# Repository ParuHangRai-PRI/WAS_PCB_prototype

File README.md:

# PCB projects related to WAS
Created March 19 2026.
Paru Hang Rai

## Handheld WAS
Schematics of the Handheld version of WAS.

## USB PD
Schematics of the Type-C integration with USB-PD using CYPD-3177. Intended as a barrel jack connector replacement.

**Always maintain appropriate gitignore before pushing**

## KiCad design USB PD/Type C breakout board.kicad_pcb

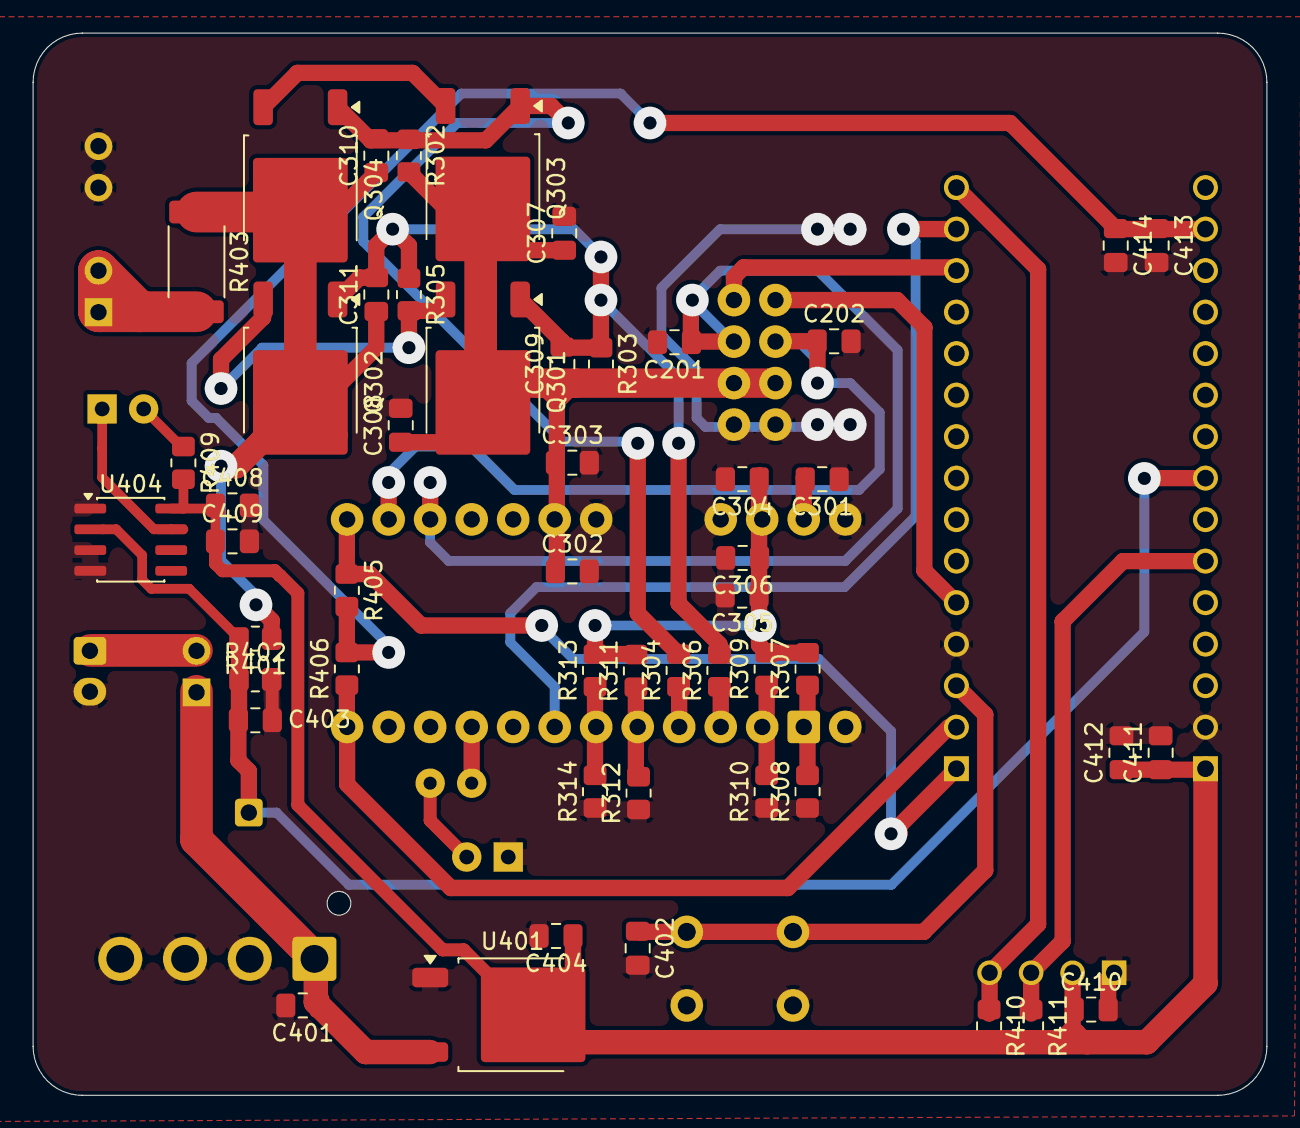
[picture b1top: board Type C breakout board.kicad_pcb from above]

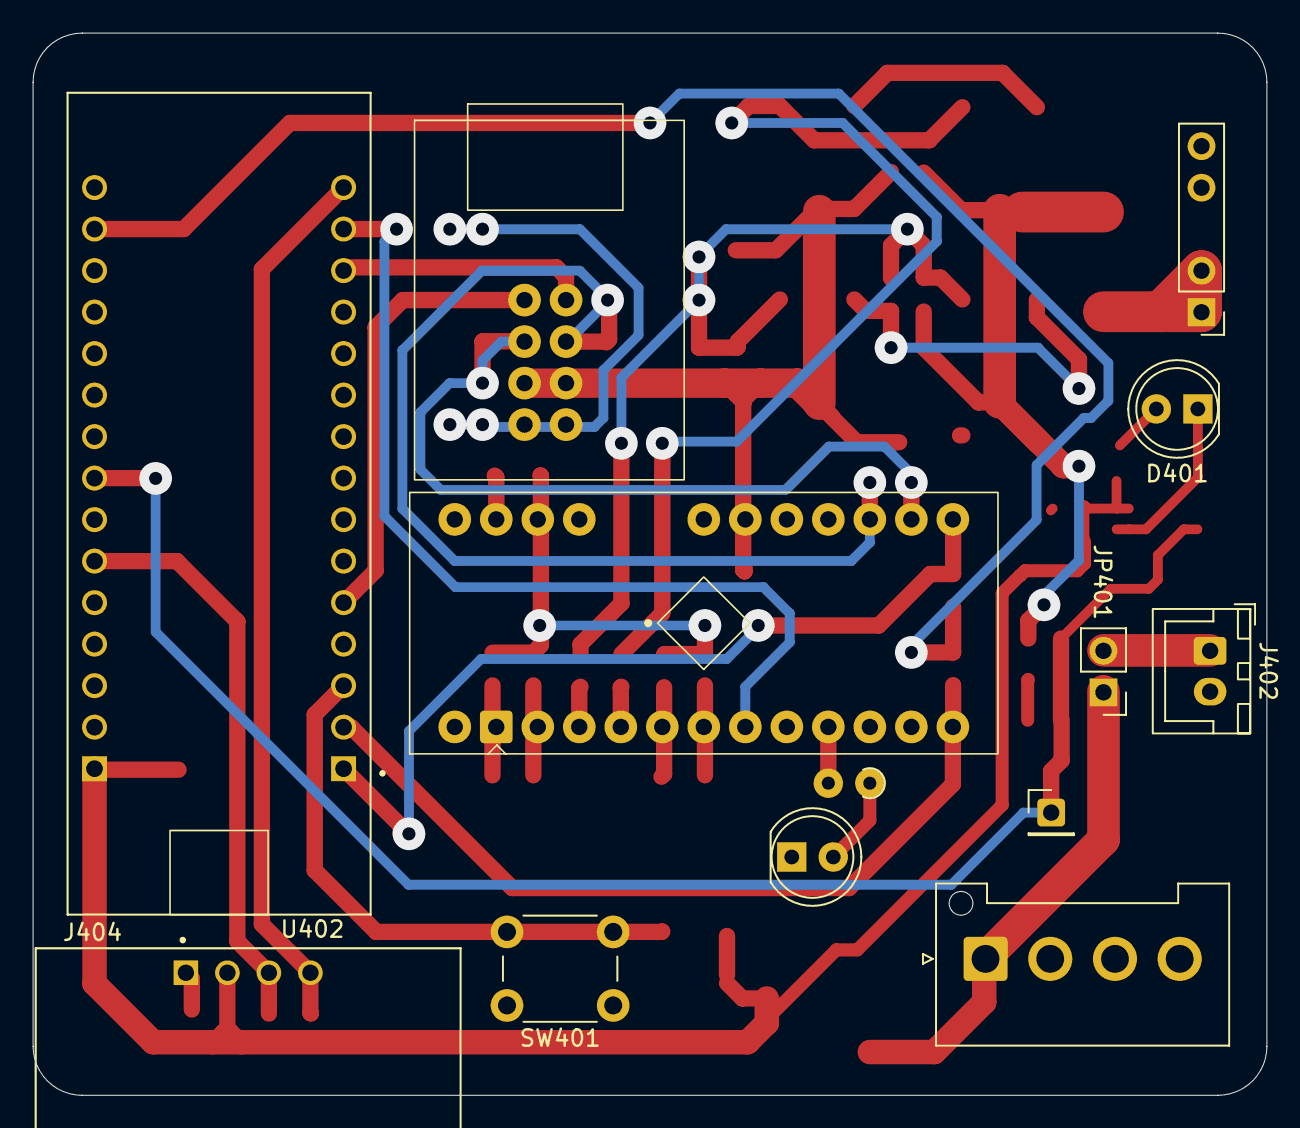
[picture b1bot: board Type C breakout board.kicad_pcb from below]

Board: 2 copper layers, 75.5 x 65.0 mm, 64 parts (13 on the bottom side), 35 nets.

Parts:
C201, C202: 330P; C_0805_2012Metric_Pad1.18x1.45mm_HandSolder
C301, C304, C307, C308, C309, C310, C311, C402, C403, C412, C413: 1u; C_0805_2012Metric_Pad1.18x1.45mm_HandSolder
C302, C401, C408: 10u; C_0805_2012Metric_Pad1.18x1.45mm_HandSolder
C303, C305, C306, C409, C410, C411, C414: 0.1u; C_0805_2012Metric_Pad1.18x1.45mm_HandSolder
C404: 22u; C_0805_2012Metric_Pad1.18x1.45mm_HandSolder
D301: LED; LED_D5.0mm
D401: LED-RED; LED_D5.0mm
J201: USB_C; Custom_USB_C
J401: Conn_01x04; JST_VH_B4P-VH-FB-B_1x04_P3.96mm_Vertical
J402: Conn_01x02; JST_XH_B2B-XH-A_1x02_P2.50mm_Vertical
J403: Conn_01x04; PinHeader_1x05_P2.54mm_Vertical
J404: OLED-Mount; OLED_0.96
JP401: Jumper_2_Open; PinHeader_1x02_P2.54mm_Vertical
Q301, Q302, Q303, Q304: PJD35P03; TO-252-2
R301: 220; R_Axial_DIN0204_L3.6mm_D1.6mm_P1.90mm_Vertical
R302, R305: 47k; R_0805_2012Metric_Pad1.20x1.40mm_HandSolder
R303: 10k; R_0805_2012Metric_Pad1.20x1.40mm_HandSolder
R304, R306: 1k; R_0805_2012Metric_Pad1.20x1.40mm_HandSolder
R307, R308, R309, R310, R311, R312, R313, R314: 5.1k; R_0805_2012Metric_Pad1.20x1.40mm_HandSolder
R401: 42k; R_0805_2012Metric_Pad1.20x1.40mm_HandSolder
R402: 8k; R_0805_2012Metric_Pad1.20x1.40mm_HandSolder
R403: 0.022R; R_2512_6332Metric_Pad1.40x3.35mm_HandSolder
R405, R406: 2.2k; R_0805_2012Metric_Pad1.20x1.40mm_HandSolder
R409: 150; R_0805_2012Metric_Pad1.20x1.40mm_HandSolder
R410, R411: 5k1; R_0805_2012Metric_Pad1.20x1.40mm_HandSolder
SW401: SW_Push; SW_PUSH_6mm_H4.3mm
TP401: TestPoint; PinHeader_1x01_P2.54mm_Vertical
U301: CYPD3177-24LQ; QFN_24-DIP
U401: AZ1117-5.0; TO-252-2
U402: NUCLEO-L432KC; MODULE_NUCLEO-L432KC
U404: LM311; SOIC-8_3.9x4.9mm_P1.27mm

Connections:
+3.3V: C304.1, C305.1, C306.1, R307.2, R309.2, R311.2, R313.2, U301.23 (VDDD)
+3V3_stm: C413.1, C414.1, R405.2, R406.2, U402.CN4_14 (+3V3)
+5V: C404.1, C408.1, C409.1, C410.1, C411.1, C412.1, J404.2, R409.2, R410.2, R411.2, U401.2 (VO), U402.CN4_1 (VIN), U404.8 (V+)
/CYPDD3177/+1.8V: C301.2, U301.24 (VCCD)
/CYPDD3177/FET_EN: R306.1, U301.3 (VBUS_FET_EN)
/CYPDD3177/FLT: R301.2, U301.9 (FAULT)
/CYPDD3177/IADJ_MAX: R311.1, R312.2, U301.5 (ISNK_COARSE)
/CYPDD3177/IADJ_MIN: R313.1, R314.2, U301.6 (ISNK_FINE)
/CYPDD3177/SAFE_EN: R304.1, U301.4 (SAFE_PWR_EN)
/CYPDD3177/VADJ_MAX: R309.1, R310.2, U301.2 (VBUS_MAX)
/CYPDD3177/VADJ_MIN: R307.1, R308.2, U301.1 (VBUS_MIN)
/test_ckt/NRST: C402.1, SW401.2, U402.CN3_3 (NRST_CN3)
/test_ckt/Vusb: C403.1, R401.2, R402.1, TP401.1 (1_1), U402.CN4_8 (PA5), U404.2 (+)
CC1: C201.1, J201.A5 (CC1), U301.15 (CC1)
CC2: C202.1, J201.B5 (CC2), U301.14 (CC2)
D+: J201.A6 (D+), J201.B6 (D+), U402.CN3_5 (PA12)
D-: J201.A7 (D-), J201.B7 (D-), U402.CN3_13 (PA11)
GND: C201.2, C202.2, C301.1, C302.2, C303.2, C304.2, C305.2, C306.2, C307.2, C308.2, C401.2, C402.2, C403.2, C404.2, C408.2, C409.2, C410.2, C411.2, C412.2, C413.2, C414.2, D301.1 (K), J201.A1 (GND), J201.A12 (GND), J201.B1 (GND), J201.B12 (GND), J401.2, J401.3, J401.4, J402.2, J403.3, J403.4, J404.1, R308.1, R310.1, R312.1, R314.1, R402.2, SW401.1, U301.19 (GND), U301.22 (GND), U301.25 (GND), U401.1 (GND), U402.CN3_4 (GND_CN3), U402.CN4_2 (GND_CN4), U404.1 (GND), U404.3 (-), U404.4 (V-)
I2C_INT: U301.7 (~HPI_INT), U402.CN3_14 (PB5)
unnamed: D301.2 (A), R301.1
unnamed: D401.2 (A), R409.1
unnamed: D401.1 (K), U404.7
unnamed: C309.2, C311.2, Q301.1 (G), Q302.1 (G), R303.1, R305.1, R306.2
unnamed: Q301.3 (S), Q302.3 (S), R305.2
unnamed: C310.2, Q303.1 (G), Q304.1 (G), R302.1, R304.2
unnamed: Q303.3 (S), Q304.3 (S)
PD_SCL: R405.1, U301.13 (HPI_SCL), U402.CN3_1 (PA9)
PD_SDA: R406.1, U301.12 (HPI_SDA), U402.CN3_2 (PA10)
SCL: J404.3, R411.1, U402.CN4_6 (PA7)
SDA: J404.4, R410.1, U402.CN3_15 (PB4)
VBUS: C302.1, C303.1, C307.1, C308.1, C309.1, J201.A4 (VBUS), J201.A9 (VBUS), J201.B4 (VBUS), J201.B9 (VBUS), Q301.2 (D), Q303.2 (D), R302.2, R303.2, U301.18 (VBUS_IN)
VCC: C401.1, J401.1, JP401.1 (A), U401.3 (VI)
Vboost: J402.1, JP401.2 (B)
Vdrive: J403.1, J403.2, R403.2
Vout: C310.1, C311.1, Q302.2 (D), Q304.2 (D), R401.1, R403.1

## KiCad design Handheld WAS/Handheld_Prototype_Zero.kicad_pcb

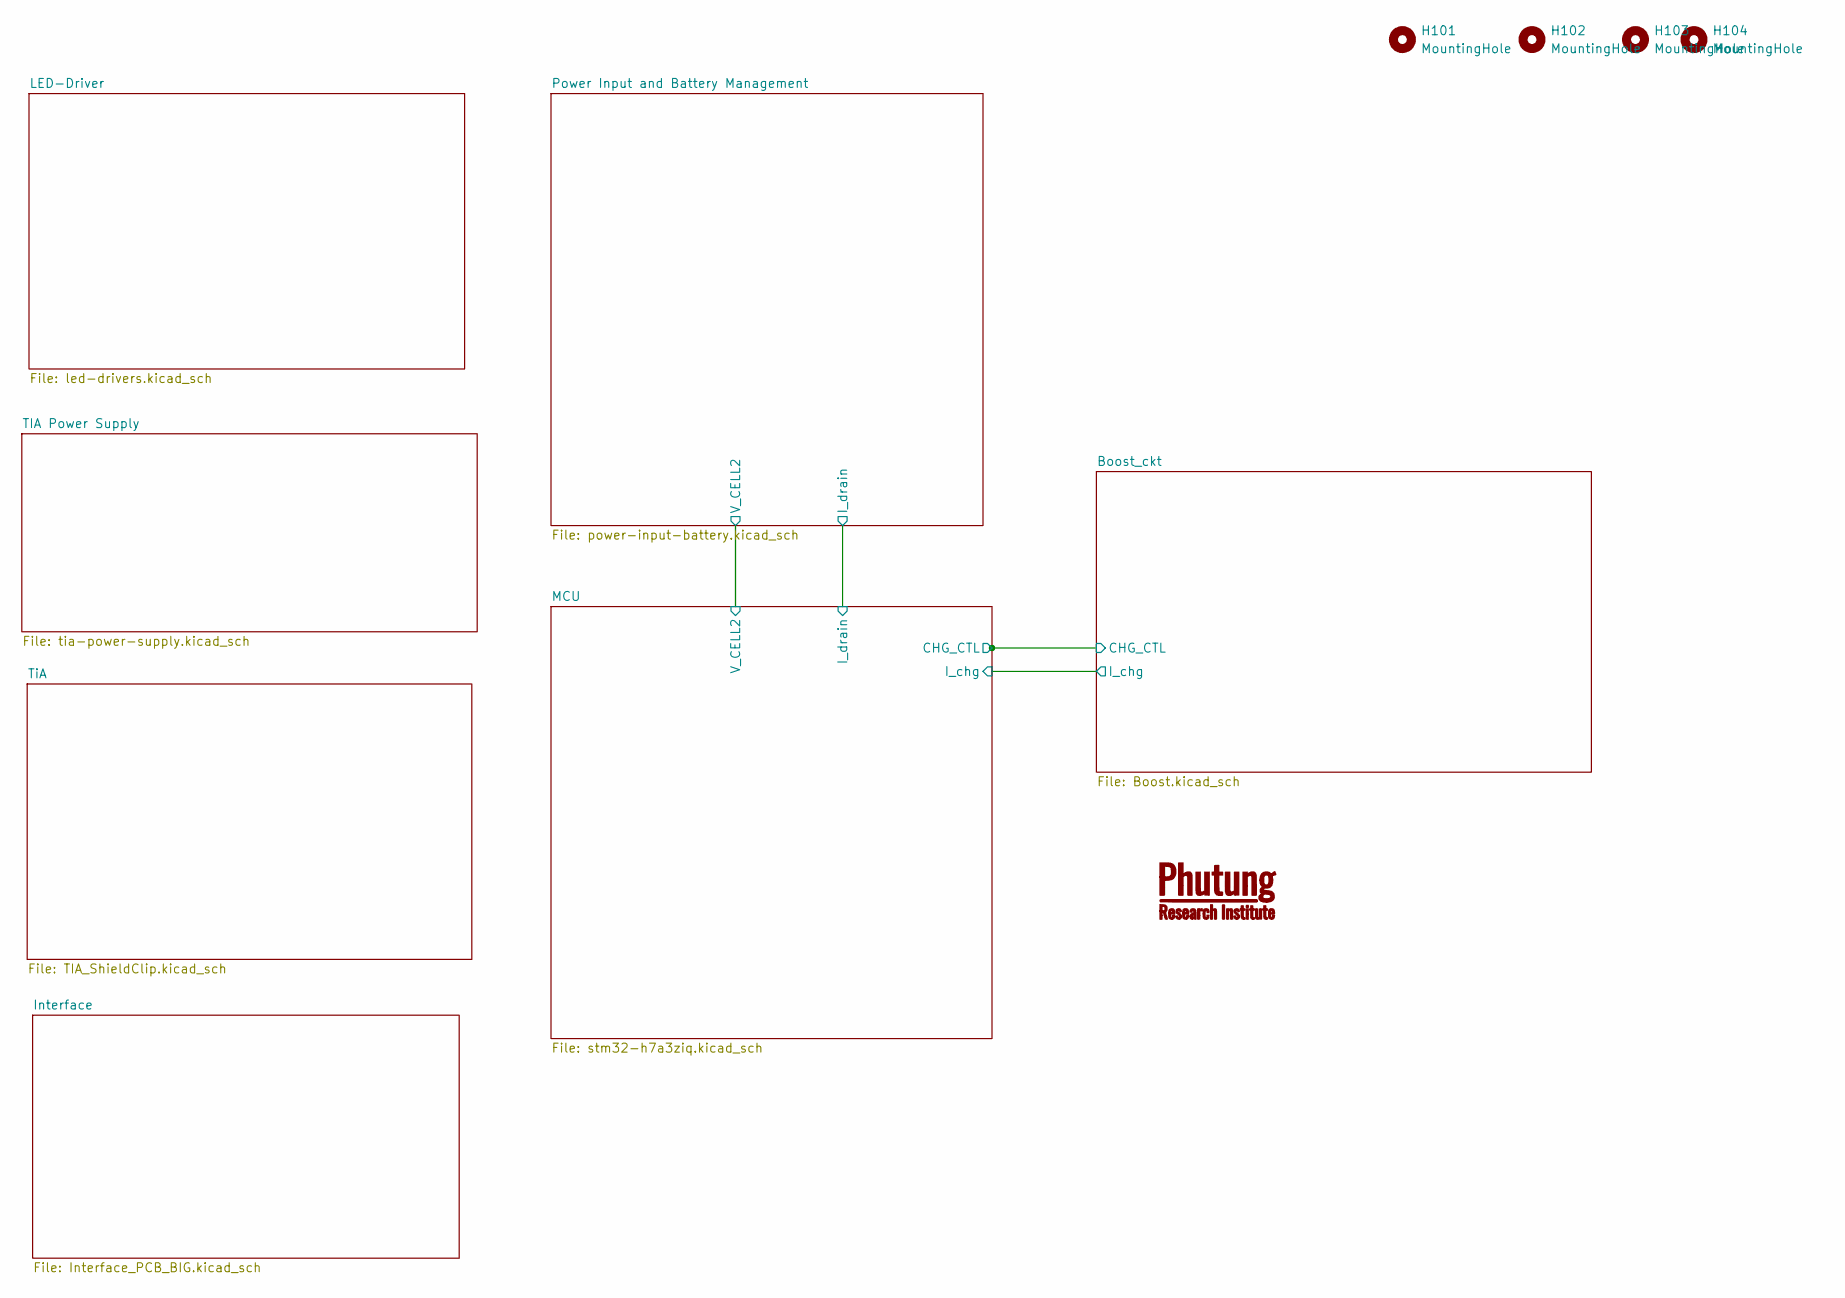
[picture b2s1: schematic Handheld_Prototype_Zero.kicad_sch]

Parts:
H101, H102, H103, H104: MountingHole; MountingHole_3.2mm_M3

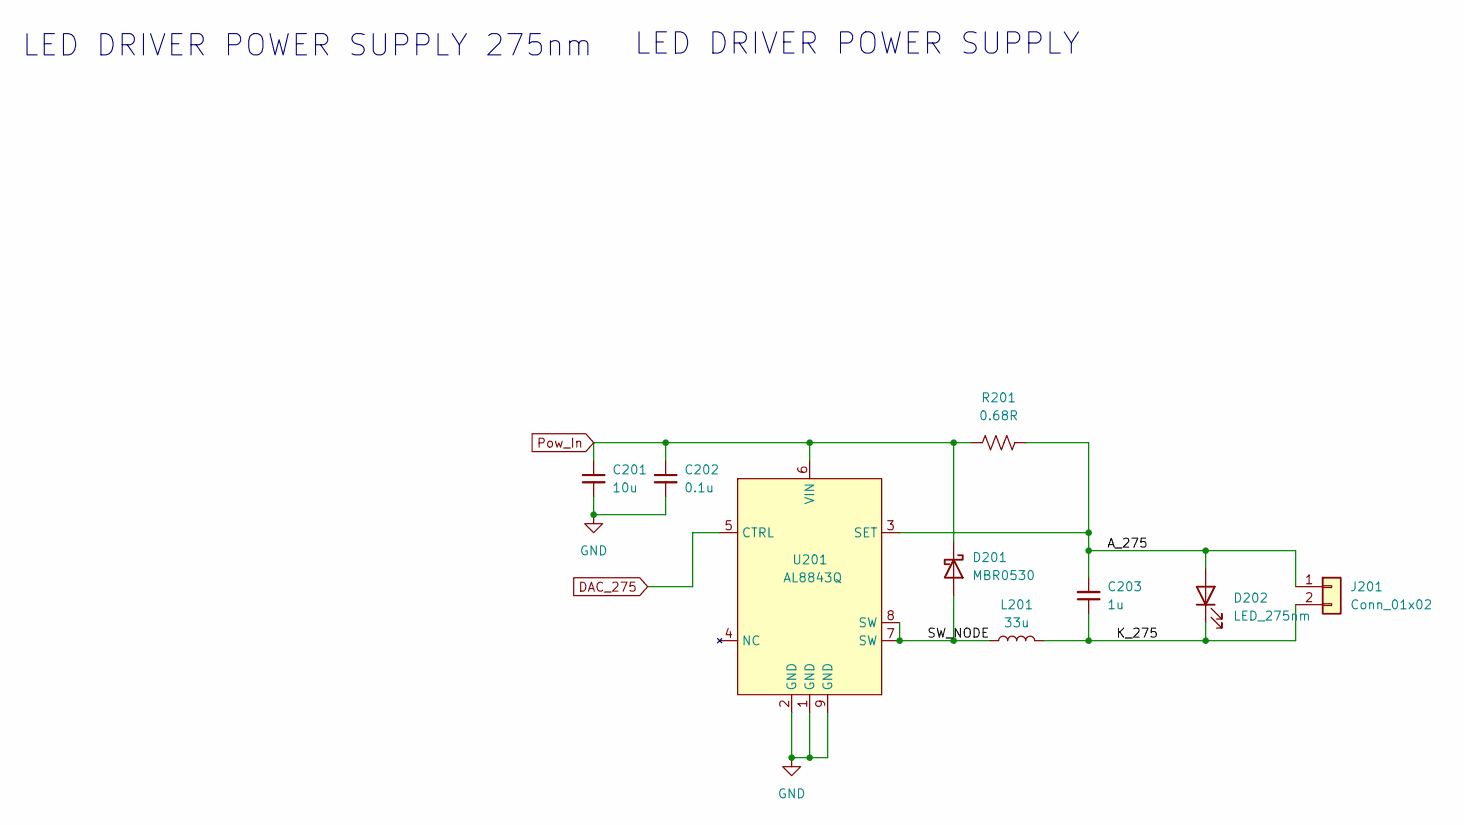
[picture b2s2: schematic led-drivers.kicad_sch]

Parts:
C201: 10u; C_0603_1608Metric_Pad1.08x0.95mm_HandSolder; JLC Part# C96446
C202: 0.1u; C_0603_1608Metric_Pad1.08x0.95mm_HandSolder; JLC Part# C1591
C203: 1u; C_0603_1608Metric_Pad1.08x0.95mm_HandSolder; JLC Part# C29936
D201: MBR0530; D_SOD-123; JLC Part# C77336
D202: LED_275nm; JST_XH_B2B-XH-A_1x02_P2.50mm_Vertical; JLC Part# x
J201: Conn_01x02; PinHeader_1x02_P2.54mm_Vertical
L201: 33u; 33u inductor
R201: 0.68R; R_1206_3216Metric_Pad1.30x1.75mm_HandSolder; JLC Part# C19108
U201: AL8843Q; SOIC-8-1EP_3.9x4.9mm_P1.27mm_EP2.41x3.3mm_ThermalVias; JLC Part# C510553

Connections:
/LED-Driver/A_275: C203.2, D202.2 (A), J201.1, R201.2, U201.3 (SET)
/LED-Driver/K_275: C203.1, D202.1 (K), J201.2, L201.2
/LED-Driver/SW_NODE: D201.2 (A), L201.1, U201.7 (SW), U201.8 (SW)
DAC_275: U201.5 (CTRL); also elsewhere on the board
GND: C201.2, C202.2, U201.1 (GND), U201.2 (GND), U201.9 (GND); also elsewhere on the board
Pow_In: C201.1, C202.1, D201.1 (K), R201.1, U201.6 (VIN); also elsewhere on the board

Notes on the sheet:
LED DRIVER POWER SUPPLY 275nm
LED DRIVER POWER SUPPLY

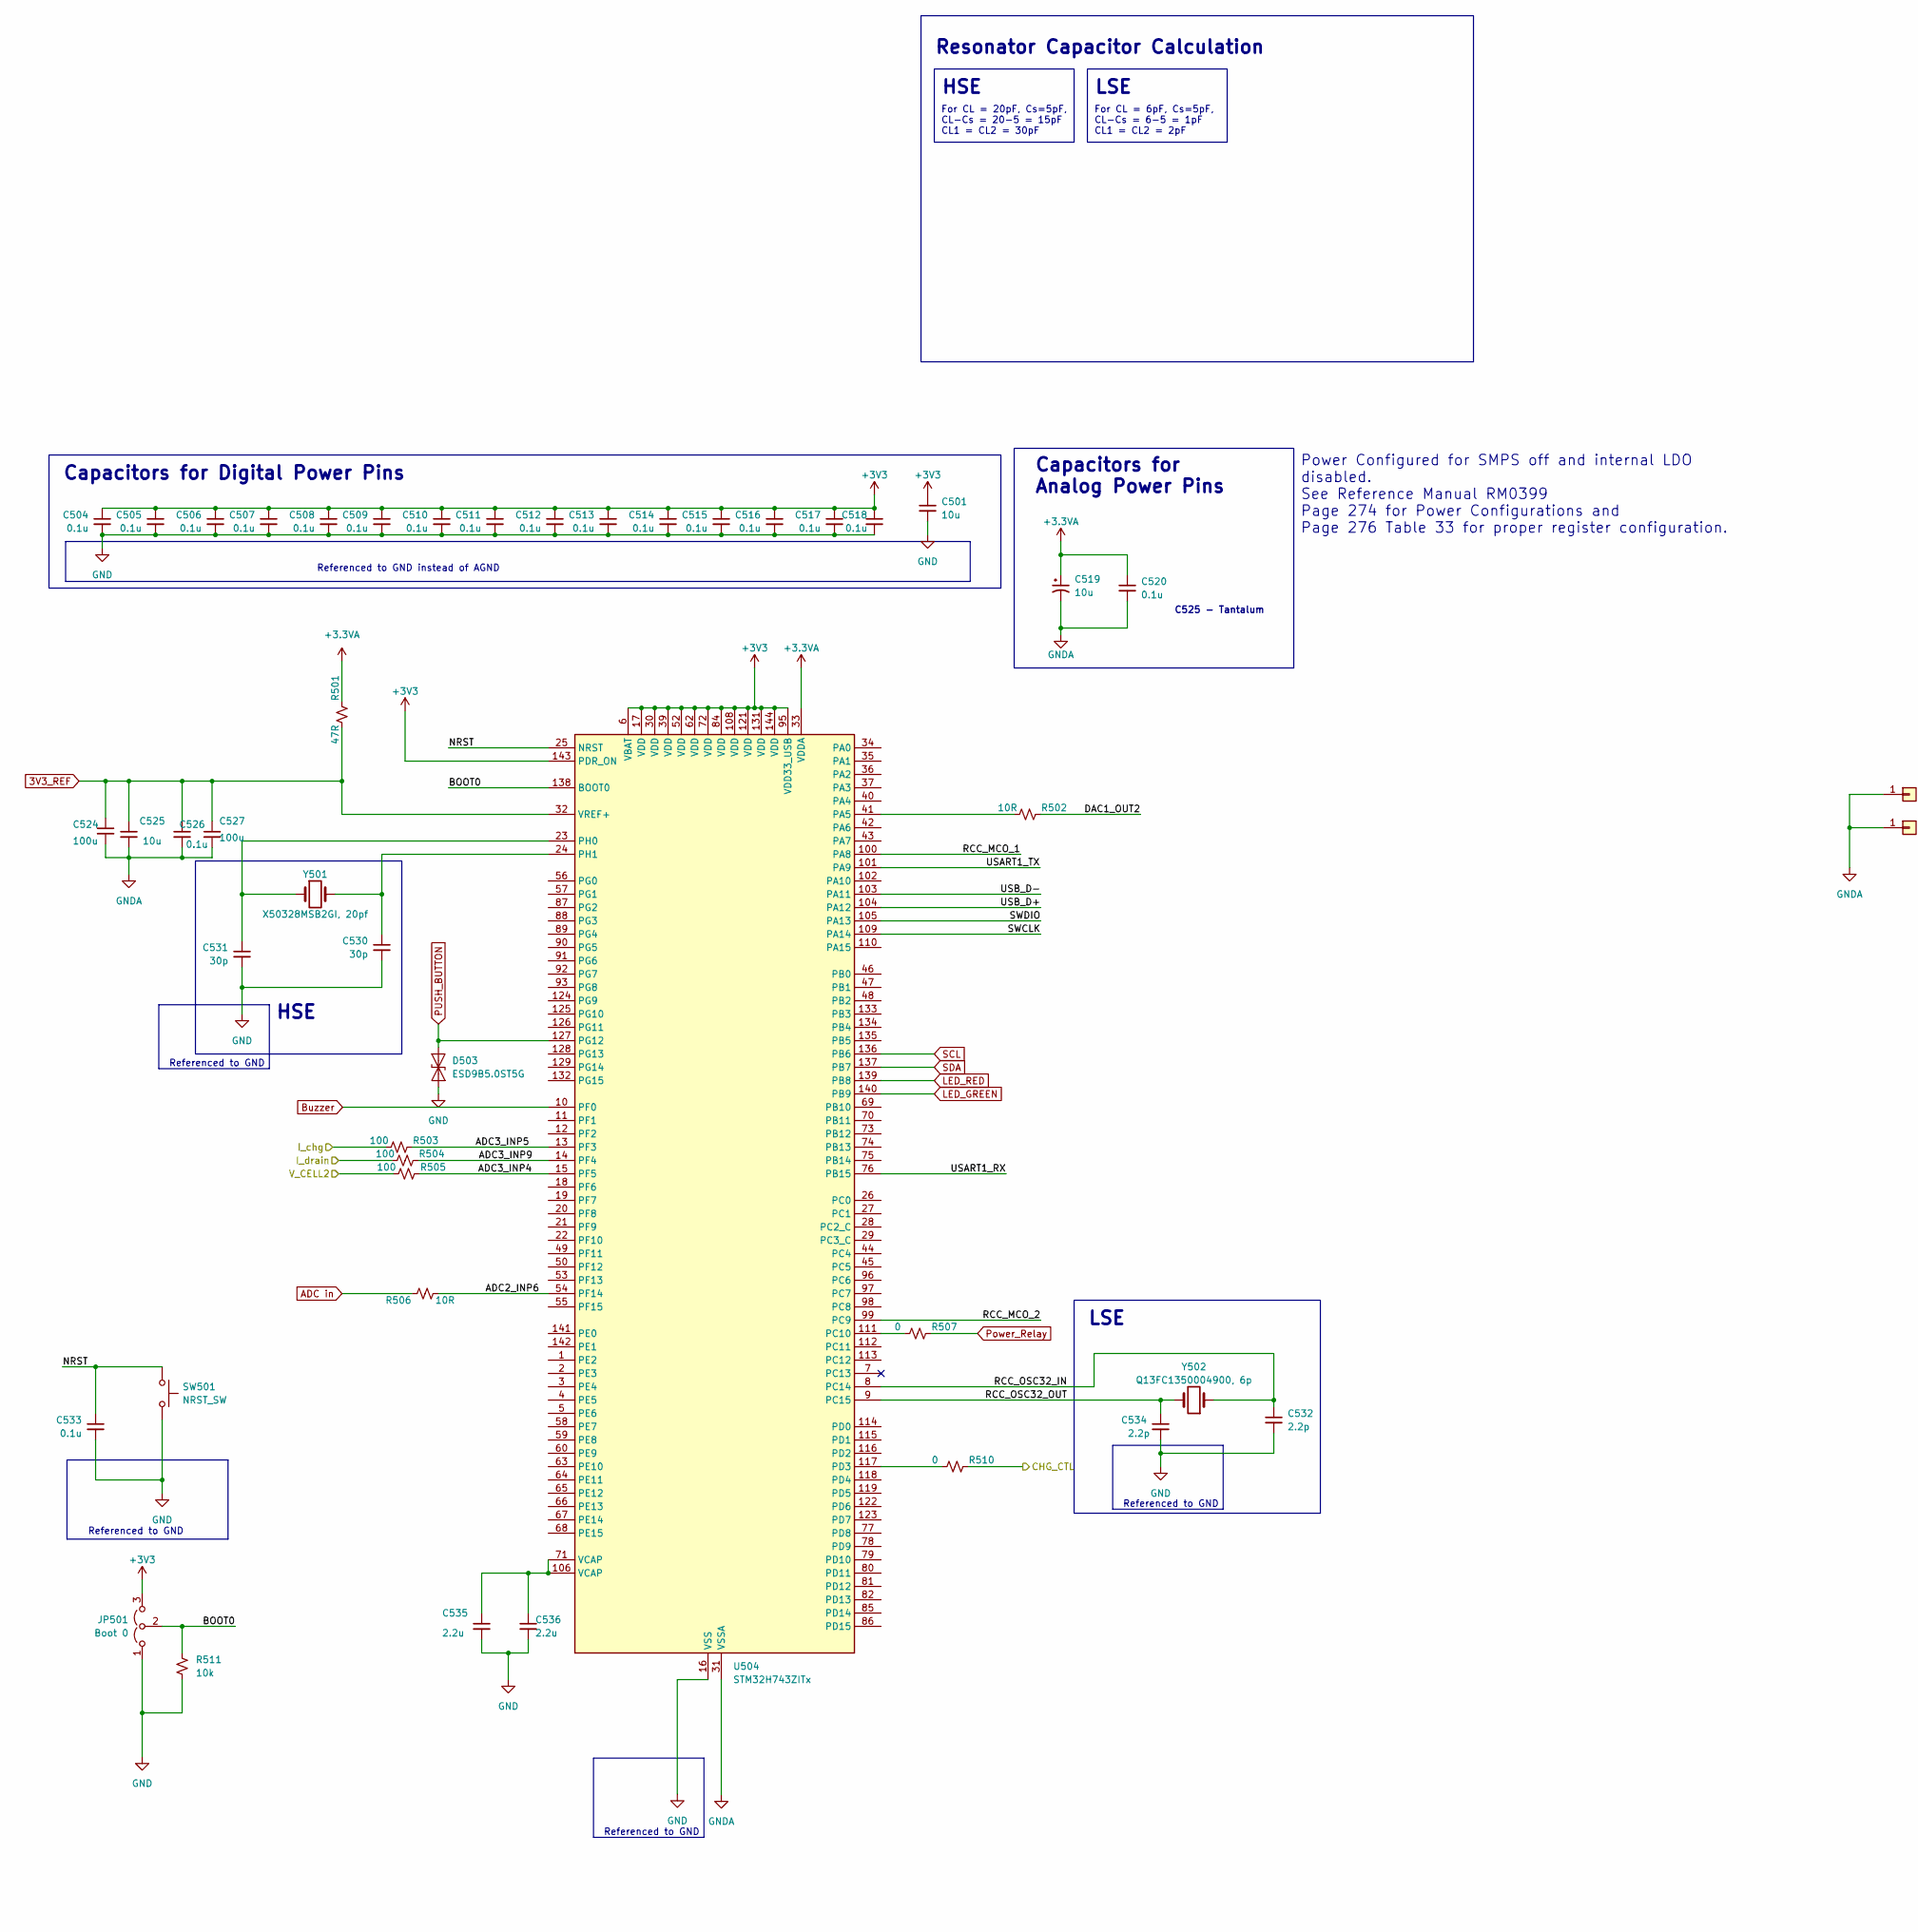
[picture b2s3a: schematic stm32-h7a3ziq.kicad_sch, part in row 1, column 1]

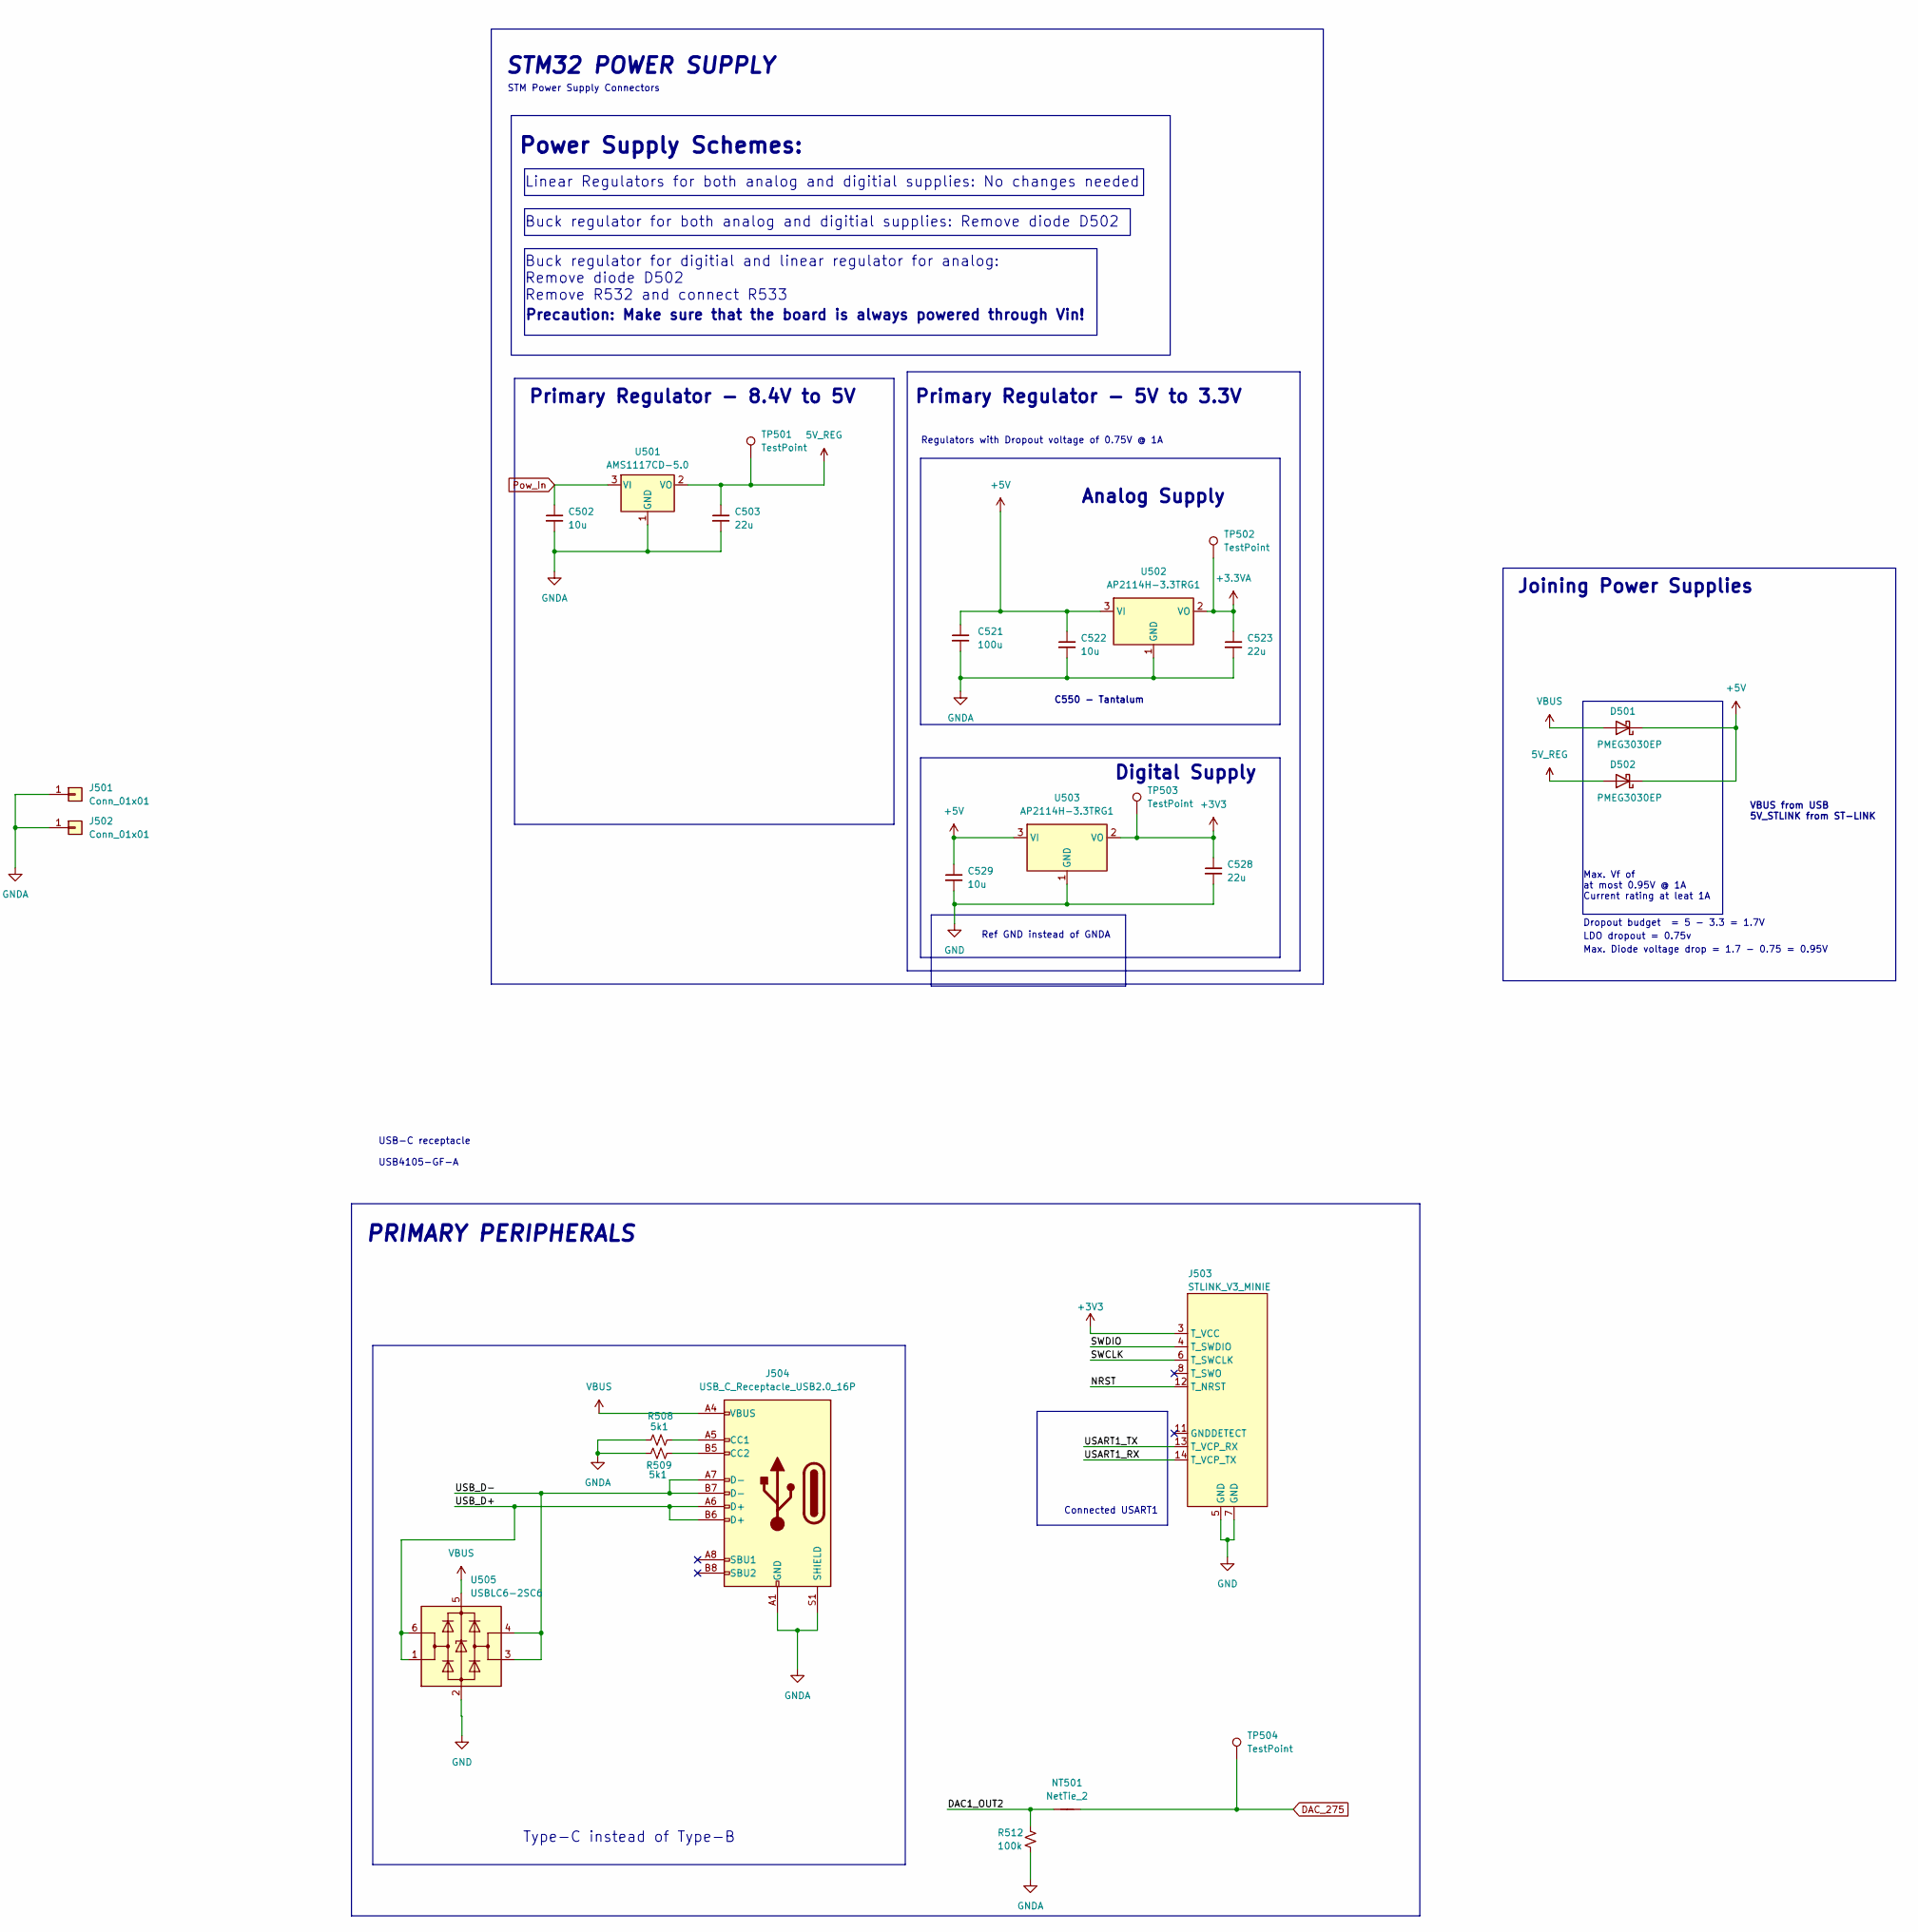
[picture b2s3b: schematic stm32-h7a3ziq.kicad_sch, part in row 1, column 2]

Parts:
C501, C525: 10u; C_0402_1005Metric_Pad0.74x0.62mm_HandSolder; JLC Part# C315248
C502, C522, C529: 10u; C_0603_1608Metric_Pad1.08x0.95mm_HandSolder; JLC Part# C96446
C503, C523, C528: 22u; C_0603_1608Metric_Pad1.08x0.95mm_HandSolder; JLC Part# C2762594
C504, C505, C506, C507, C508, C509, C510, C511, C512, C513, C514, C515, C516, C517, C518, C520, C526, C533: 0.1u; C_0402_1005Metric_Pad0.74x0.62mm_HandSolder; JLC Part# C1581
C519: 10u; C_0805_2012Metric_Pad1.18x1.45mm_HandSolder; JLC Part# C1969735
C521, C524, C527: 100u; C_1210_3225Metric_Pad1.33x2.70mm_HandSolder; JLC Part# C5372270
C530, C531: 30p; C_0402_1005Metric_Pad0.74x0.62mm_HandSolder; JLC Part# C1570
C532, C534: 2.2p; C_0402_1005Metric_Pad0.74x0.62mm_HandSolder; JLC Part# C1559
C535, C536: 2.2u; C_0402_1005Metric_Pad0.74x0.62mm_HandSolder; JLC Part# C170151
D501, D502: PMEG3030EP; D_SOD-128; JLC Part# C255587
D503: ESD9B5.0ST5G; D_SOD-923; JLC Part# C111566
J501, J502: Conn_01x01; TestPoint_Pad_D1.5mm
J503: STLINK_V3_MINIE; CONN_3220-14-0300-00_CNC
J504: USB_C_Receptacle_USB2.0_16P; USB-C-SMD_TYPEC-304J-BCP16; JLC Part# C2765186
JP501: Boot 0; 3 pad
NT501: NetTie_2; NetTie-2_SMD_Pad0.5mm
R501: 47R; R_0402_1005Metric_Pad0.72x0.64mm_HandSolder; JLC Part# C6458739
R502, R506: 10R; R_0402_1005Metric_Pad0.72x0.64mm_HandSolder; JLC Part# C25077
R503, R504, R505: 100; R_0402_1005Metric_Pad0.72x0.64mm_HandSolder; JLC Part# C850722
R507, R510: 0; R_0402_1005Metric_Pad0.72x0.64mm_HandSolder; JLC Part# C60485
R508, R509: 5k1; R_0402_1005Metric_Pad0.72x0.64mm_HandSolder; JLC Part# C25905
R511: 10k; R_0402_1005Metric_Pad0.72x0.64mm_HandSolder; JLC Part# C850723
R512: 100k; R_0402_1005Metric_Pad0.72x0.64mm_HandSolder; JLC Part# C25741
SW501: NRST_SW; SW-SMD_L3.9-W3.0-P4.45; JLC Part# C720477
TP501, TP502, TP503, TP504: TestPoint; TestPoint_Pad_D1.5mm
U501: AMS1117CD-5.0; TO-252-2; JLC Part# C347250
U502, U503: AP2114H-3.3TRG1; SOT-223-3_TabPin2; JLC Part# C150716
U504: STM32H743ZITx; LQFP-144_20x20mm_P0.5mm; JLC Part# C114408
U505: USBLC6-2SC6; SOT-23-6_Handsoldering; JLC Part# C2687116
Y501: X50328MSB2GI, 20pf; Crystal_SMD_5032-2Pin_5.0x3.2mm; JLC Part# C115962
Y502: Q13FC1350004900, 6p; Crystal_SMD_3215-2Pin_3.2x1.5mm; JLC Part# C95361

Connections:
3V3_REF: C524.1, C525.1, C526.1, C527.1, R501.1, U504.32 (VREF+)
5V_REG: C503.1, D502.2 (A), TP501.1, U501.2 (VO)
+3.3VA: C519.1, C520.1, C523.1, R501.2, TP502.1, U502.2 (VO), U504.33 (VDDA)
+3V3: C501.1, C504.1, C505.1, C506.1, C507.1, C508.1, C509.1, C510.1, C511.1, C512.1, C513.1, C514.1, C515.1, C516.1, C517.1, C518.1, C528.1, J503.3 (T_VCC), JP501.3 (B), TP503.1, U503.2 (VO), U504.6 (VBAT), U504.17 (VDD), U504.30 (VDD), U504.39 (VDD), U504.52 (VDD), U504.62 (VDD), U504.72 (VDD), U504.84 (VDD), U504.95 (VDD33_USB), U504.108 (VDD), U504.121 (VDD), U504.131 (VDD), U504.143 (PDR_ON), U504.144 (VDD); also elsewhere on the board
+5V: C521.1, C522.1, C529.1, D501.1 (K), D502.1 (K), U502.3 (VI), U503.3 (VI); also elsewhere on the board
/Boost_ckt/CHG_CTL: R510.2; also elsewhere on the board
/Boost_ckt/I_chg: R503.1; also elsewhere on the board
/MCU/ADC2_INP6: R506.1, U504.54 (PF14)
/MCU/ADC3_INP4: R505.2, U504.15 (PF5)
/MCU/ADC3_INP5: R503.2, U504.13 (PF3)
/MCU/ADC3_INP9: R504.2, U504.14 (PF4)
/MCU/BOOT0: JP501.2 (C), R511.1, U504.138 (BOOT0)
/MCU/DAC1_OUT2: NT501.1, R502.2, R512.1
/MCU/NRST: C533.1, J503.12 (T_NRST), SW501.2, U504.25 (NRST)
/MCU/RCC_MCO_1: U504.100 (PA8)
/MCU/RCC_MCO_2: U504.99 (PC9)
/MCU/RCC_OSC32_IN: C532.1, U504.8 (PC14), Y502.1
/MCU/RCC_OSC32_OUT: C534.1, U504.9 (PC15), Y502.2
/MCU/SWCLK: J503.6 (T_SWCLK), U504.109 (PA14)
/MCU/SWDIO: J503.4 (T_SWDIO), U504.105 (PA13)
/MCU/USART1_RX: J503.14 (T_VCP_TX), U504.76 (PB15)
/MCU/USART1_TX: J503.13 (T_VCP_RX), U504.101 (PA9)
/MCU/USB_D+: J504.A6 (D+), J504.B6 (D+), U504.104 (PA12), U505.1 (I/O1), U505.6 (I/O1)
/MCU/USB_D-: J504.A7 (D-), J504.B7 (D-), U504.103 (PA11), U505.3 (I/O2), U505.4 (I/O2)
/MCU/V_CELL2: R505.1; also elsewhere on the board
/Power Input and Battery Management/I_drain: R504.1; also elsewhere on the board
ADC in: R506.2; also elsewhere on the board
Buzzer: U504.10 (PF0); also elsewhere on the board
DAC_275: NT501.2, TP504.1; also elsewhere on the board
GND: C501.2, C504.2, C505.2, C506.2, C507.2, C508.2, C509.2, C510.2, C511.2, C512.2, C513.2, C514.2, C515.2, C516.2, C517.2, C518.2, C528.2, C529.2, C530.2, C531.2, C532.2, C533.2, C534.2, C535.2, C536.2, D503.1 (A1), J503.5 (GND), J503.7 (GND), JP501.1 (A), R511.2, SW501.1, U503.1 (GND), U504.16 (VSS), U504.38 (VSS), U504.51 (VSS), U504.61 (VSS), U504.83 (VSS), U504.94 (VSS), U504.107 (VSS), U504.120 (VSS), U504.130 (VSS), U505.2 (GND); also elsewhere on the board
GNDA: C502.2, C503.2, C519.2, C520.2, C521.2, C522.2, C523.2, C524.2, C525.2, C526.2, C527.2, J501.1, J502.1, J504.A1 (GND), J504.A12 (GND), J504.B1 (GND), J504.B12 (GND), J504.S1 (SHIELD), R508.2, R509.2, R512.2, U501.1 (GND), U502.1 (GND), U504.31 (VSSA); also elsewhere on the board
LED_GREEN: U504.140 (PB9); also elsewhere on the board
LED_RED: U504.139 (PB8); also elsewhere on the board
unnamed: C535.1, C536.1, U504.71 (VCAP), U504.106 (VCAP)
unnamed: J504.A5 (CC1), R508.1
unnamed: J504.B5 (CC2), R509.1
unnamed: R502.1, U504.41 (PA5)
unnamed: R507.1, U504.111 (PC10)
unnamed: R510.1, U504.117 (PD3)
unnamed: C531.1, U504.23 (PH0), Y501.1
unnamed: C530.1, U504.24 (PH1), Y501.2
PUSH_BUTTON: D503.2 (A2), U504.127 (PG12); also elsewhere on the board
Pow_In: C502.1, U501.3 (VI); also elsewhere on the board
Power_Relay: R507.2; also elsewhere on the board
SCL: U504.136 (PB6); also elsewhere on the board
SDA: U504.137 (PB7); also elsewhere on the board
VBUS: D501.2 (A), J504.A4 (VBUS), J504.A9 (VBUS), J504.B4 (VBUS), J504.B9 (VBUS), U505.5 (VBUS); also elsewhere on the board

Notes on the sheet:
Primary Regulator - 8.4V to 5V
HSE
Regulators with Dropout voltage of 0.75V @ 1A
Type-C instead of Type-B
Referenced to GND
LDO dropout = 0.75v
Referenced to GND
PRIMARY PERIPHERALS
Buck regulator for both analog and digitial supplies: Remove diode D502
STM32 POWER SUPPLY
LSE
Max. Diode voltage drop = 1.7 - 0.75 = 0.95V
Referenced to GND instead of AGND
Ref GND instead of GNDA
Linear Regulators for both analog and digitial supplies: No changes needed
Precaution: Make sure that the board is always powered through Vin!
Resonator Capacitor Calculation
Dropout budget = 5 - 3.3 = 1.7V
Capacitors for Analog Power Pins
Joining Power Supplies
C550 - Tantalum
Power Configured for SMPS off and internal LDO disabled. See Reference Manual RM0399 Page 274 for Power Configurations and Page 276 Table 33 for proper register configuration.
For CL = 6pF, Cs=5pF, CL-Cs = 6-5 = 1pF CL1 = CL2 = 2pF
Capacitors for Digital Power Pins
Max. Vf of at most 0.95V @ 1A Current rating at leat 1A
For CL = 20pF, Cs=5pF, CL-Cs = 20-5 = 15pF CL1 = CL2 = 30pF
Connected USART1
Digital Supply
STM Power Supply Connectors
VBUS from USB 5V_STLINK from ST-LINK
Primary Regulator - 5V to 3.3V
C525 - Tantalum
Analog Supply
USB-C receptacle USB4105-GF-A
Buck regulator for digitial and linear regulator for analog: Remove diode D502 Remove R532 and connect R533
Power Supply Schemes:
